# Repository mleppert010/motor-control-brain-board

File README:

May as well make a readme
Brain board for motor controller

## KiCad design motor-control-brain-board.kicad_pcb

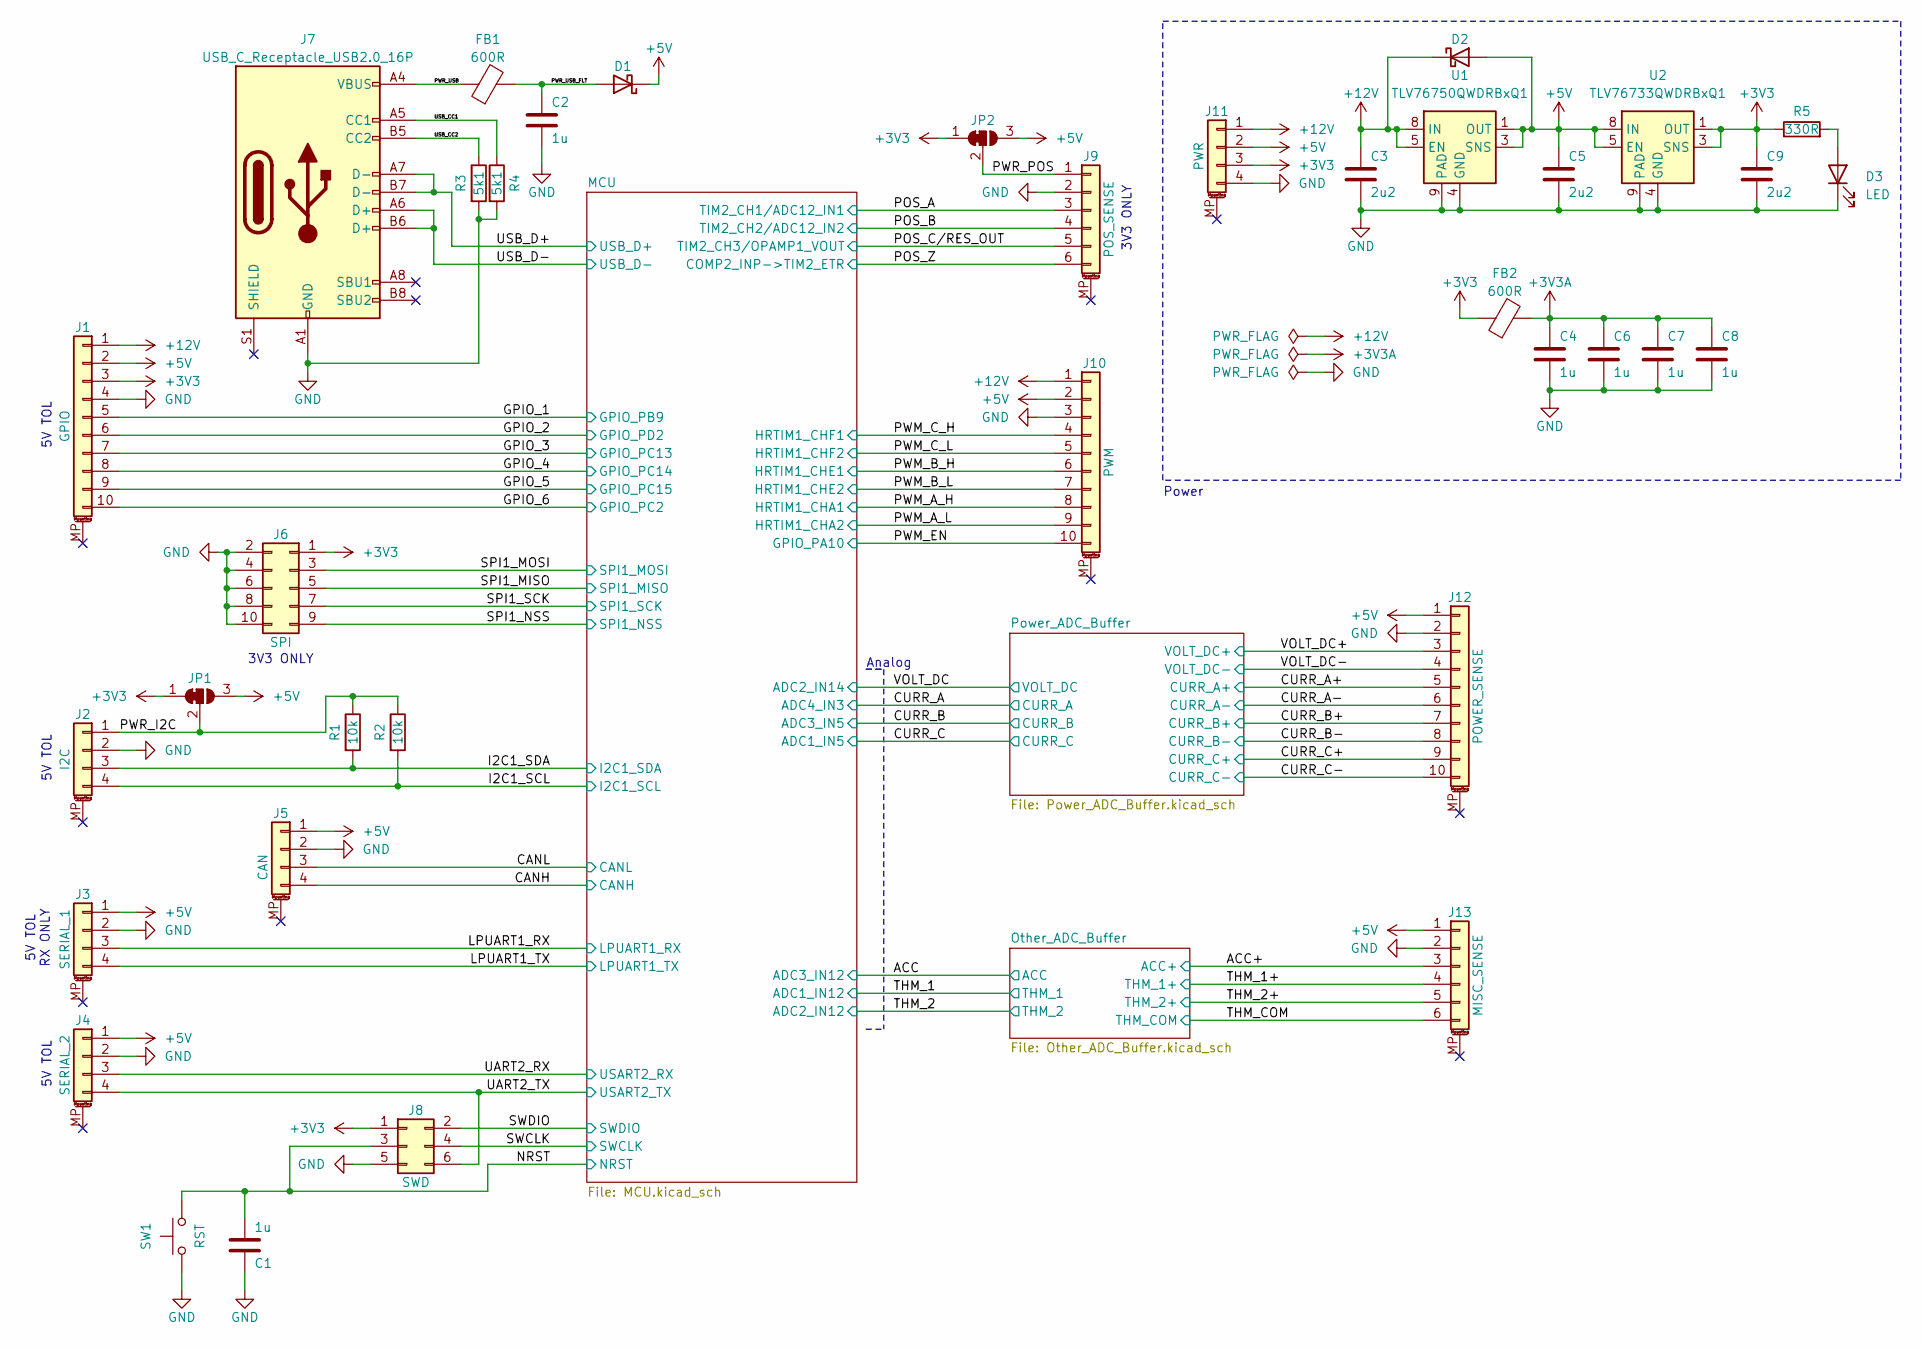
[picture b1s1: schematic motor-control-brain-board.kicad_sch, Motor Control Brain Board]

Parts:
C1, C2, C4, C6, C7, C8: 1u; C_0402_1005Metric
C3, C5, C9: 2u2; C_0603_1608Metric
D1, D2: D_Schottky; D_0402_1005Metric
D3: LED; LED_0603_1608Metric
FB1, FB2: 600R; L_0603_1608Metric
J1: GPIO; JST_GH_SM10B-GHS-TB_1x10-1MP_P1.25mm_Horizontal
J2: I2C; JST_GH_SM04B-GHS-TB_1x04-1MP_P1.25mm_Horizontal
J3: SERIAL_1; JST_GH_SM04B-GHS-TB_1x04-1MP_P1.25mm_Horizontal
J4: SERIAL_2; JST_GH_SM04B-GHS-TB_1x04-1MP_P1.25mm_Horizontal
J5: CAN; JST_GH_SM04B-GHS-TB_1x04-1MP_P1.25mm_Horizontal
J6: SPI; PinHeader_2x05_P1.27mm_Vertical
J7: USB_C_Receptacle_USB2.0_16P; USB_C_Receptacle_GCT_USB4110
J8: SWD; Tag-Connect_TC2030-IDC-FP_2x03_P1.27mm_Vertical
J9: POS_SENSE; JST_GH_SM06B-GHS-TB_1x06-1MP_P1.25mm_Horizontal
J10: PWM; JST_GH_SM10B-GHS-TB_1x10-1MP_P1.25mm_Horizontal
J11: PWR; JST_GH_SM04B-GHS-TB_1x04-1MP_P1.25mm_Horizontal
J12: POWER_SENSE; JST_GH_SM10B-GHS-TB_1x10-1MP_P1.25mm_Horizontal
J13: MISC_SENSE; JST_GH_SM06B-GHS-TB_1x06-1MP_P1.25mm_Horizontal
JP1, JP2: SolderJumper_3_Open; SolderJumper-3_P1.3mm_Bridged12_RoundedPad1.0x1.5mm
R1, R2: 10k; R_0402_1005Metric
R3, R4: 5k1; R_0402_1005Metric
R5: 330R; R_0402_1005Metric
SW1: RST; SW_SPST_PTS810
U1: TLV76750QWDRBxQ1; VSON-8-1EP_3x3mm_P0.65mm_EP1.65x2.4mm_ThermalVias
U2: TLV76733QWDRBxQ1; VSON-8-1EP_3x3mm_P0.65mm_EP1.65x2.4mm_ThermalVias

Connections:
+3V3: C9.1, FB2.1, J1.3, J6.1, J8.1, J11.3, JP1.1 (A), JP2.1 (A), R5.1, U2.1 (OUT), U2.3 (SNS); also elsewhere on the board
+3V3A: C4.1, C6.1, C7.1, C8.1, FB2.2; also elsewhere on the board
+5V: C5.1, D1.1 (K), D2.2 (A), J1.2, J3.1, J4.1, J5.1, J10.2, J11.2, J12.1, J13.1, JP1.3 (B), JP2.3 (B), U1.1 (OUT), U1.3 (SNS), U2.5 (EN), U2.8 (IN); also elsewhere on the board
+12V: C3.1, D2.1 (K), J1.1, J10.1, J11.1, U1.5 (EN), U1.8 (IN)
/ACC+: J13.3; also elsewhere on the board
/CANH: J5.4; also elsewhere on the board
/CANL: J5.3; also elsewhere on the board
/CURR_A+: J12.5; also elsewhere on the board
/CURR_A-: J12.6; also elsewhere on the board
/CURR_B+: J12.7; also elsewhere on the board
/CURR_B-: J12.8; also elsewhere on the board
/CURR_C+: J12.9; also elsewhere on the board
/CURR_C-: J12.10; also elsewhere on the board
/GPIO_1: J1.5; also elsewhere on the board
/GPIO_2: J1.6; also elsewhere on the board
/GPIO_3: J1.7; also elsewhere on the board
/GPIO_4: J1.8; also elsewhere on the board
/GPIO_5: J1.9; also elsewhere on the board
/GPIO_6: J1.10; also elsewhere on the board
/I2C1_SCL: J2.4, R2.2; also elsewhere on the board
/I2C1_SDA: J2.3, R1.2; also elsewhere on the board
/LPUART1_RX: J3.3; also elsewhere on the board
/LPUART1_TX: J3.4; also elsewhere on the board
/NRST: C1.2, J8.3, SW1.2; also elsewhere on the board
/POS_A: J9.3; also elsewhere on the board
/POS_B: J9.4; also elsewhere on the board
/POS_C/RES_OUT: J9.5; also elsewhere on the board
/POS_Z: J9.6; also elsewhere on the board
/PWM_A_H: J10.8; also elsewhere on the board
/PWM_A_L: J10.9; also elsewhere on the board
/PWM_B_H: J10.6; also elsewhere on the board
/PWM_B_L: J10.7; also elsewhere on the board
/PWM_C_H: J10.4; also elsewhere on the board
/PWM_C_L: J10.5; also elsewhere on the board
/PWM_EN: J10.10; also elsewhere on the board
/PWR_I2C: J2.1, JP1.2 (C), R1.1, R2.1
/PWR_POS: J9.1, JP2.2 (C)
/PWR_USB: FB1.1, J7.A4 (VBUS), J7.A9 (VBUS), J7.B4 (VBUS), J7.B9 (VBUS)
/PWR_USB_FLT: C2.1, D1.2 (A), FB1.2
/SPI1_MISO: J6.5; also elsewhere on the board
/SPI1_MOSI: J6.3; also elsewhere on the board
/SPI1_NSS: J6.9; also elsewhere on the board
/SPI1_SCK: J6.7; also elsewhere on the board
/SWCLK: J8.4; also elsewhere on the board
/SWDIO: J8.2; also elsewhere on the board
/THM_1+: J13.4; also elsewhere on the board
/THM_2+: J13.5; also elsewhere on the board
/UART2_RX: J4.3; also elsewhere on the board
/UART2_TX: J4.4, J8.6; also elsewhere on the board
/USB_CC1: J7.A5 (CC1), R4.1
/USB_CC2: J7.B5 (CC2), R3.1
/USB_D+: J7.A7 (D-), J7.B7 (D-); also elsewhere on the board
/USB_D-: J7.A6 (D+), J7.B6 (D+); also elsewhere on the board
/VOLT_DC+: J12.3; also elsewhere on the board
/VOLT_DC-: J12.4; also elsewhere on the board
GND: C1.1, C2.2, C3.2, C4.2, C5.2, C6.2, C7.2, C8.2, C9.2, D3.1 (K), J1.4, J2.2, J3.2, J4.2, J5.2, J6.2, J6.4, J6.6, J6.8, J6.10, J7.A1 (GND), J7.A12 (GND), J7.B1 (GND), J7.B12 (GND), J8.5, J9.2, J10.3, J11.4, J12.2, J13.2, J13.6, R3.2, R4.2, SW1.1, U1.4 (GND), U1.6 (GND), U1.9 (PAD), U2.4 (GND), U2.6 (GND), U2.9 (PAD); also elsewhere on the board
unnamed: D3.2 (A), R5.2

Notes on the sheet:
5V TOL RX ONLY
3V3 ONLY
Analog
Power
5V TOL

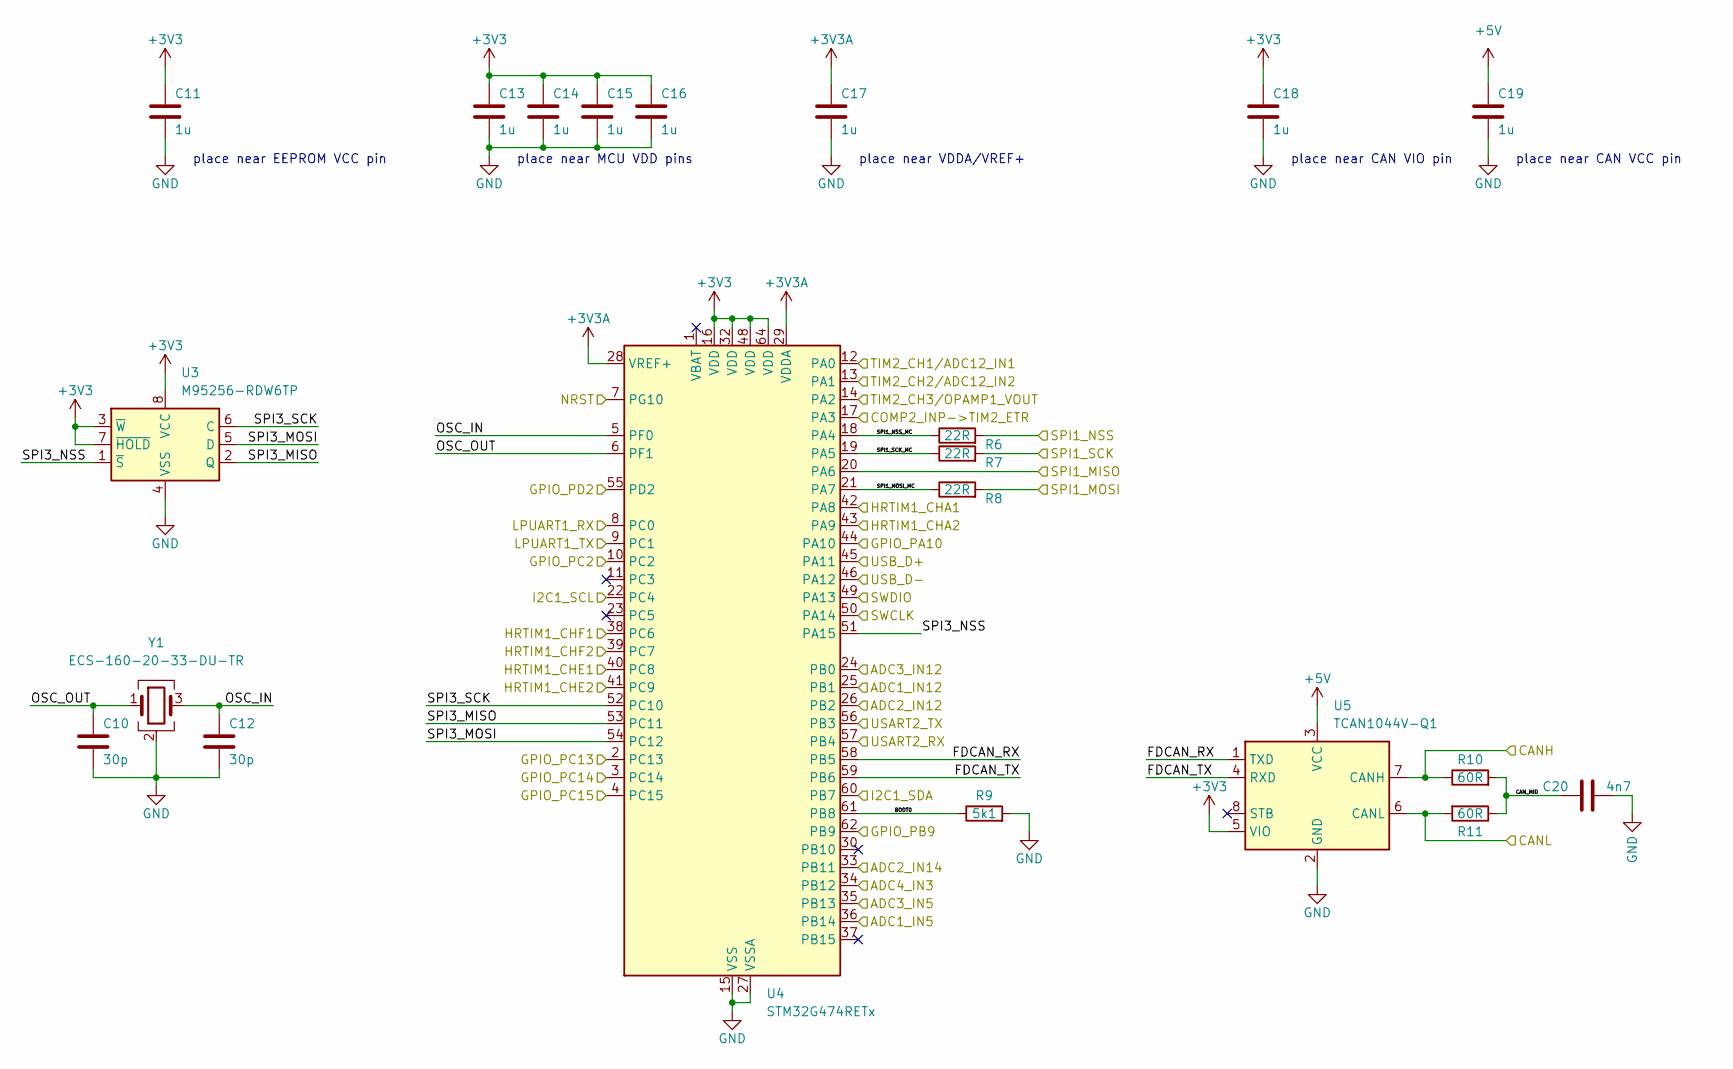
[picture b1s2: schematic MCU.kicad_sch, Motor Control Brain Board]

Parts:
C10, C12: 30p; C_0402_1005Metric
C11, C13, C14, C15, C16, C17, C18, C19: 1u; C_0402_1005Metric
C20: 4n7; C_0402_1005Metric
R6, R7, R8: 22R; R_0402_1005Metric
R9: 5k1; R_0402_1005Metric
R10, R11: 60R; R_0603_1608Metric
U3: M95256-RDW6TP; TSSOP-8_4.4x3mm_P0.65mm
U4: STM32G474RETx; LQFP-64_10x10mm_P0.5mm
U5: TCAN1044V-Q1; TSOT-23-8
Y1: ECS-160-20-33-DU-TR; Oscillator_SMD_Abracon_ASE-4Pin_3.2x2.5mm

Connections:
+3V3: C11.1, C13.1, C14.1, C15.1, C16.1, C18.1, U3.3 (~W), U3.7 (~HOLD), U3.8 (VCC), U4.16 (VDD), U4.32 (VDD), U4.48 (VDD), U4.64 (VDD), U5.5 (VIO); also elsewhere on the board
+3V3A: C17.1, U4.28 (VREF+), U4.29 (VDDA); also elsewhere on the board
+5V: C19.1, U5.3 (VCC); also elsewhere on the board
/ACC: U4.24 (PB0); also elsewhere on the board
/CANH: R10.1, U5.7 (CANH); also elsewhere on the board
/CANL: R11.2, U5.6 (CANL); also elsewhere on the board
/CURR_A: U4.34 (PB12); also elsewhere on the board
/CURR_B: U4.35 (PB13); also elsewhere on the board
/CURR_C: U4.36 (PB14); also elsewhere on the board
/GPIO_1: U4.62 (PB9); also elsewhere on the board
/GPIO_2: U4.55 (PD2); also elsewhere on the board
/GPIO_3: U4.2 (PC13); also elsewhere on the board
/GPIO_4: U4.3 (PC14); also elsewhere on the board
/GPIO_5: U4.4 (PC15); also elsewhere on the board
/GPIO_6: U4.10 (PC2); also elsewhere on the board
/I2C1_SCL: U4.22 (PC4); also elsewhere on the board
/I2C1_SDA: U4.60 (PB7); also elsewhere on the board
/LPUART1_RX: U4.8 (PC0); also elsewhere on the board
/LPUART1_TX: U4.9 (PC1); also elsewhere on the board
/MCU/BOOT0: R9.1, U4.61 (PB8)
/MCU/CAN_MID: C20.1, R10.2, R11.1
/MCU/FDCAN_RX: U4.58 (PB5), U5.1 (TXD)
/MCU/FDCAN_TX: U4.59 (PB6), U5.4 (RXD)
/MCU/OSC_IN: C12.1, U4.5 (PF0), Y1.3
/MCU/OSC_OUT: C10.1, U4.6 (PF1), Y1.1
/MCU/SPI1_MOSI_MC: R8.1, U4.21 (PA7)
/MCU/SPI1_NSS_MC: R6.1, U4.18 (PA4)
/MCU/SPI1_SCK_MC: R7.1, U4.19 (PA5)
/MCU/SPI3_MISO: U3.2 (Q), U4.53 (PC11)
/MCU/SPI3_MOSI: U3.5 (D), U4.54 (PC12)
/MCU/SPI3_NSS: U3.1 (~S), U4.51 (PA15)
/MCU/SPI3_SCK: U3.6 (C), U4.52 (PC10)
/NRST: U4.7 (PG10); also elsewhere on the board
/POS_A: U4.12 (PA0); also elsewhere on the board
/POS_B: U4.13 (PA1); also elsewhere on the board
/POS_C/RES_OUT: U4.14 (PA2); also elsewhere on the board
/POS_Z: U4.17 (PA3); also elsewhere on the board
/PWM_A_H: U4.42 (PA8); also elsewhere on the board
/PWM_A_L: U4.43 (PA9); also elsewhere on the board
/PWM_B_H: U4.40 (PC8); also elsewhere on the board
/PWM_B_L: U4.41 (PC9); also elsewhere on the board
/PWM_C_H: U4.38 (PC6); also elsewhere on the board
/PWM_C_L: U4.39 (PC7); also elsewhere on the board
/PWM_EN: U4.44 (PA10); also elsewhere on the board
/SPI1_MISO: U4.20 (PA6); also elsewhere on the board
/SPI1_MOSI: R8.2; also elsewhere on the board
/SPI1_NSS: R6.2; also elsewhere on the board
/SPI1_SCK: R7.2; also elsewhere on the board
/SWCLK: U4.50 (PA14); also elsewhere on the board
/SWDIO: U4.49 (PA13); also elsewhere on the board
/THM_1: U4.25 (PB1); also elsewhere on the board
/THM_2: U4.26 (PB2); also elsewhere on the board
/UART2_RX: U4.57 (PB4); also elsewhere on the board
/UART2_TX: U4.56 (PB3); also elsewhere on the board
/USB_D+: U4.45 (PA11); also elsewhere on the board
/USB_D-: U4.46 (PA12); also elsewhere on the board
/VOLT_DC: U4.33 (PB11); also elsewhere on the board
GND: C10.2, C11.2, C12.2, C13.2, C14.2, C15.2, C16.2, C17.2, C18.2, C19.2, C20.2, R9.2, U3.4 (VSS), U4.15 (VSS), U4.27 (VSSA), U4.31 (VSS), U4.47 (VSS), U4.63 (VSS), U5.2 (GND), Y1.2 (G), Y1.4 (G); also elsewhere on the board

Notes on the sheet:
place near EEPROM VCC pin
place near MCU VDD pins
place near VDDA/VREF+
place near CAN VIO pin
place near CAN VCC pin

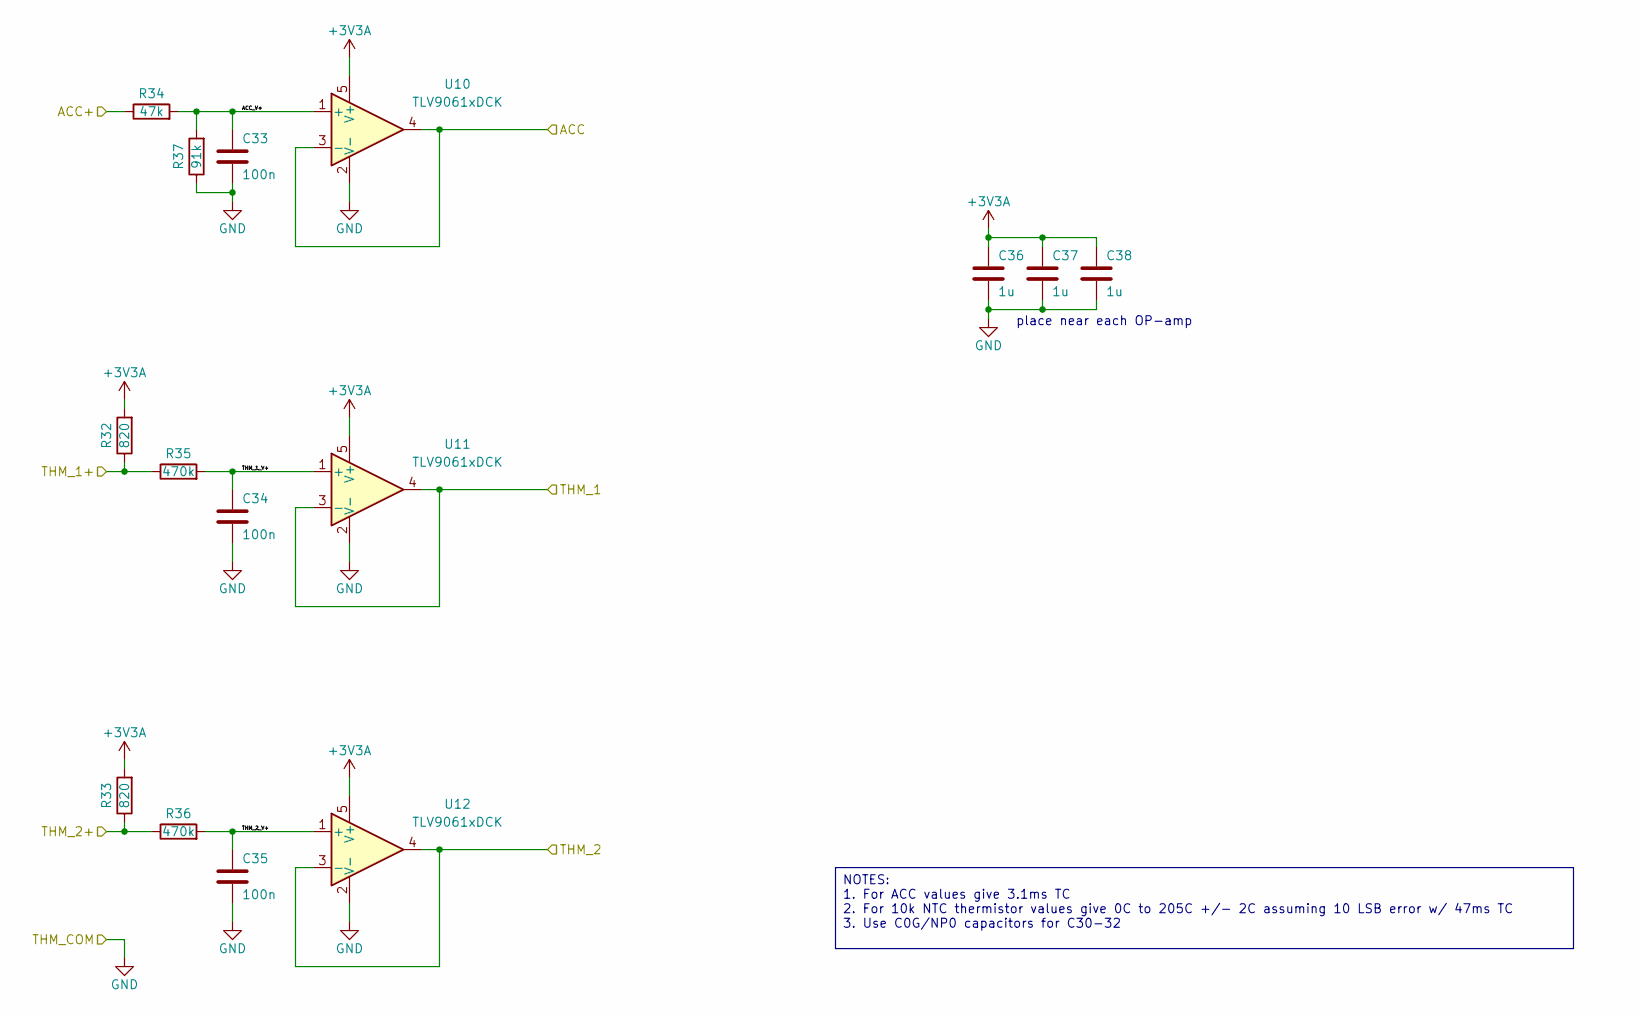
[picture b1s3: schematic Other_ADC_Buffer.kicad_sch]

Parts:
C33, C34, C35: 100n; C_0603_1608Metric
C36, C37, C38: 1u; C_0402_1005Metric
R32, R33: 820; R_0603_1608Metric
R34: 47k; R_0603_1608Metric
R35, R36: 470k; R_0603_1608Metric
R37: 91k; R_0603_1608Metric
U10, U11, U12: TLV9061xDCK; SOT-353_SC-70-5

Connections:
+3V3A: C36.1, C37.1, C38.1, R32.2, R33.2, U10.5 (V+), U11.5 (V+), U12.5 (V+); also elsewhere on the board
/ACC: U10.3 (-), U10.4; also elsewhere on the board
/ACC+: R34.1; also elsewhere on the board
/Other_ADC_Buffer/ACC_V+: C33.1, R34.2, R37.2, U10.1 (+)
/Other_ADC_Buffer/THM_1_V+: C34.1, R35.2, U11.1 (+)
/Other_ADC_Buffer/THM_2_V+: C35.1, R36.2, U12.1 (+)
/THM_1: U11.3 (-), U11.4; also elsewhere on the board
/THM_1+: R32.1, R35.1; also elsewhere on the board
/THM_2: U12.3 (-), U12.4; also elsewhere on the board
/THM_2+: R33.1, R36.1; also elsewhere on the board
GND: C33.2, C34.2, C35.2, C36.2, C37.2, C38.2, R37.1, U10.2 (V-), U11.2 (V-), U12.2 (V-); also elsewhere on the board

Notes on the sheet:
place near each OP-amp
NOTES: 1. For ACC values give 3.1ms TC 2. For 10k NTC thermistor values give 0C to 205C +/- 2C assuming 10 LSB error w/ 47ms TC 3. Use C0G/NP0 capacitors for C30-32

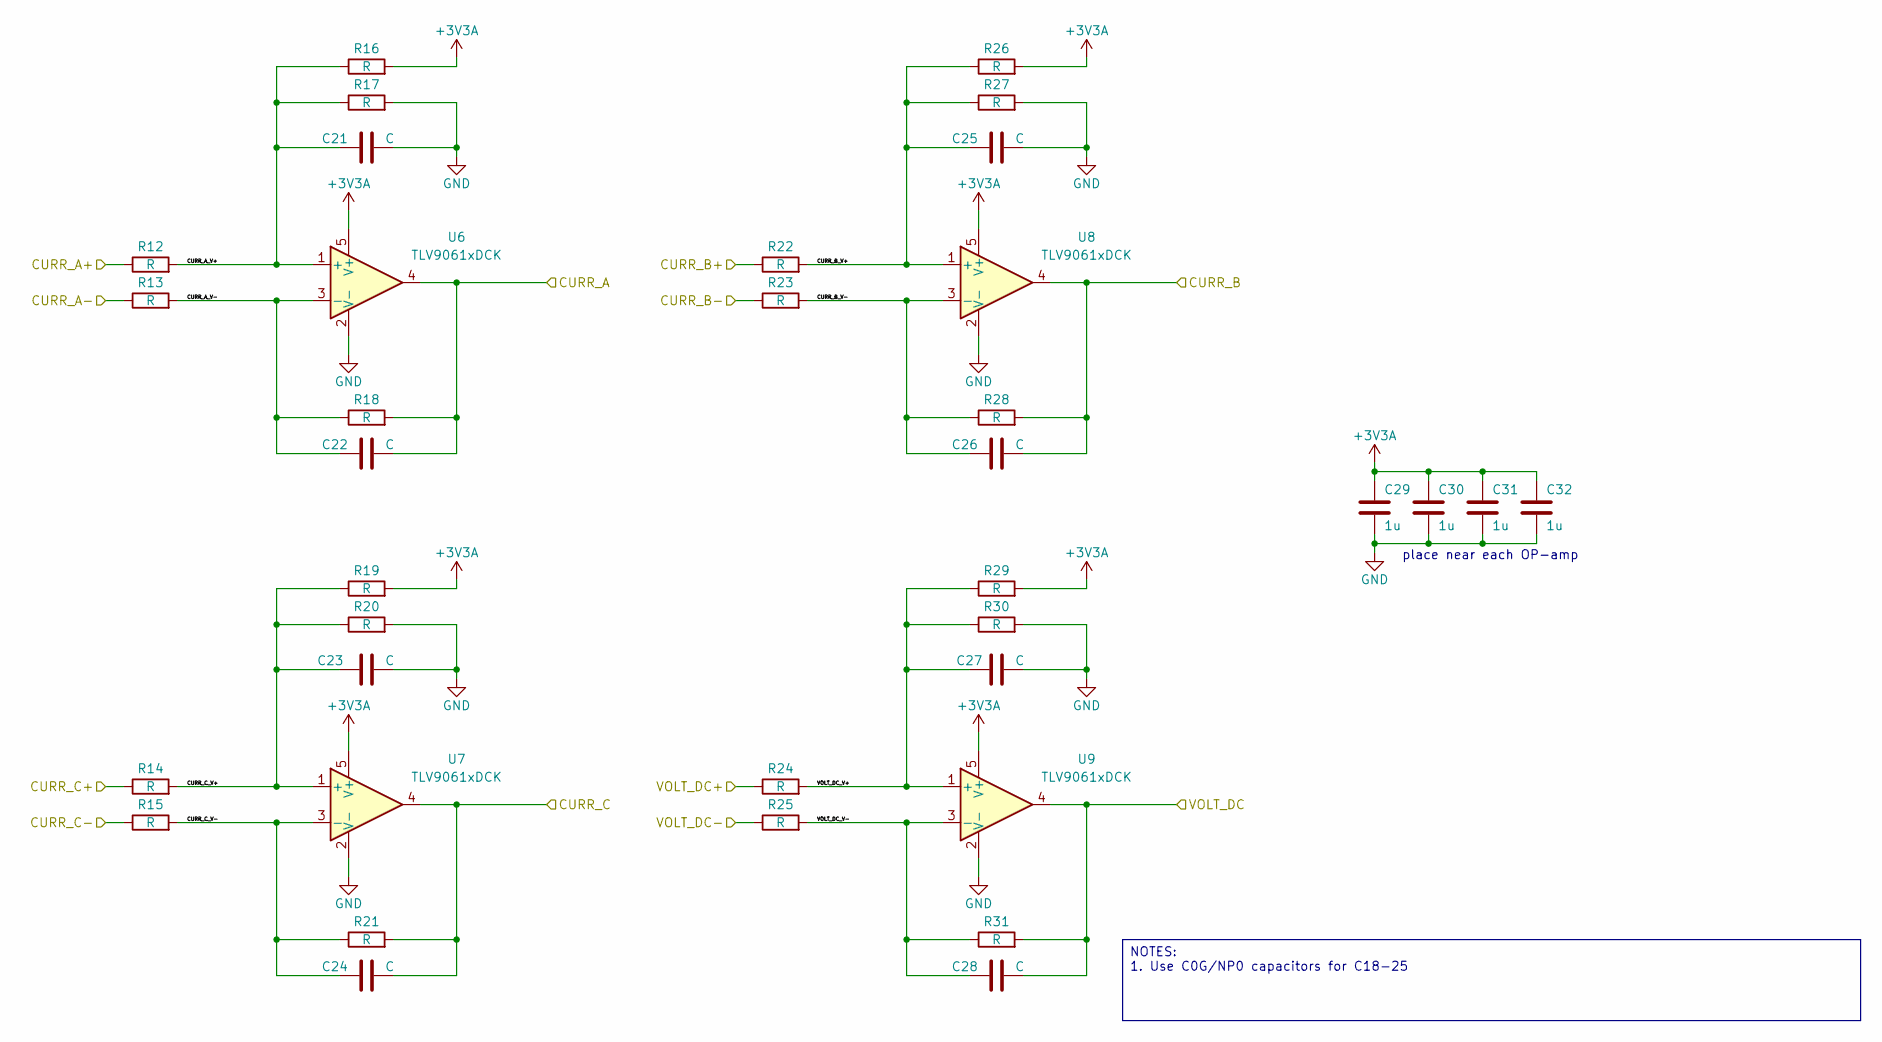
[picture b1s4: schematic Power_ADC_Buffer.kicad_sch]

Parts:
C21, C22, C23, C24, C25, C26, C27, C28: C; C_0603_1608Metric
C29, C30, C31, C32: 1u; C_0402_1005Metric
R12, R13, R14, R15, R16, R17, R18, R19, R20, R21, R22, R23, R24, R25, R26, R27, R28, R29, R30, R31: R; R_0603_1608Metric
U6, U7, U8, U9: TLV9061xDCK; SOT-353_SC-70-5

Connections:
+3V3A: C29.1, C30.1, C31.1, C32.1, R16.2, R19.2, R26.2, R29.2, U6.5 (V+), U7.5 (V+), U8.5 (V+), U9.5 (V+); also elsewhere on the board
/CURR_A: C22.2, R18.2, U6.4; also elsewhere on the board
/CURR_A+: R12.1; also elsewhere on the board
/CURR_A-: R13.1; also elsewhere on the board
/CURR_B: C26.2, R28.2, U8.4; also elsewhere on the board
/CURR_B+: R22.1; also elsewhere on the board
/CURR_B-: R23.1; also elsewhere on the board
/CURR_C: C24.2, R21.2, U7.4; also elsewhere on the board
/CURR_C+: R14.1; also elsewhere on the board
/CURR_C-: R15.1; also elsewhere on the board
/Power_ADC_Buffer/CURR_A_V+: C21.1, R12.2, R16.1, R17.1, U6.1 (+)
/Power_ADC_Buffer/CURR_A_V-: C22.1, R13.2, R18.1, U6.3 (-)
/Power_ADC_Buffer/CURR_B_V+: C25.1, R22.2, R26.1, R27.1, U8.1 (+)
/Power_ADC_Buffer/CURR_B_V-: C26.1, R23.2, R28.1, U8.3 (-)
/Power_ADC_Buffer/CURR_C_V+: C23.1, R14.2, R19.1, R20.1, U7.1 (+)
/Power_ADC_Buffer/CURR_C_V-: C24.1, R15.2, R21.1, U7.3 (-)
/Power_ADC_Buffer/VOLT_DC_V+: C27.1, R24.2, R29.1, R30.1, U9.1 (+)
/Power_ADC_Buffer/VOLT_DC_V-: C28.1, R25.2, R31.1, U9.3 (-)
/VOLT_DC: C28.2, R31.2, U9.4; also elsewhere on the board
/VOLT_DC+: R24.1; also elsewhere on the board
/VOLT_DC-: R25.1; also elsewhere on the board
GND: C21.2, C23.2, C25.2, C27.2, C29.2, C30.2, C31.2, C32.2, R17.2, R20.2, R27.2, R30.2, U6.2 (V-), U7.2 (V-), U8.2 (V-), U9.2 (V-); also elsewhere on the board

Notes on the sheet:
place near each OP-amp
NOTES: 1. Use C0G/NP0 capacitors for C18-25

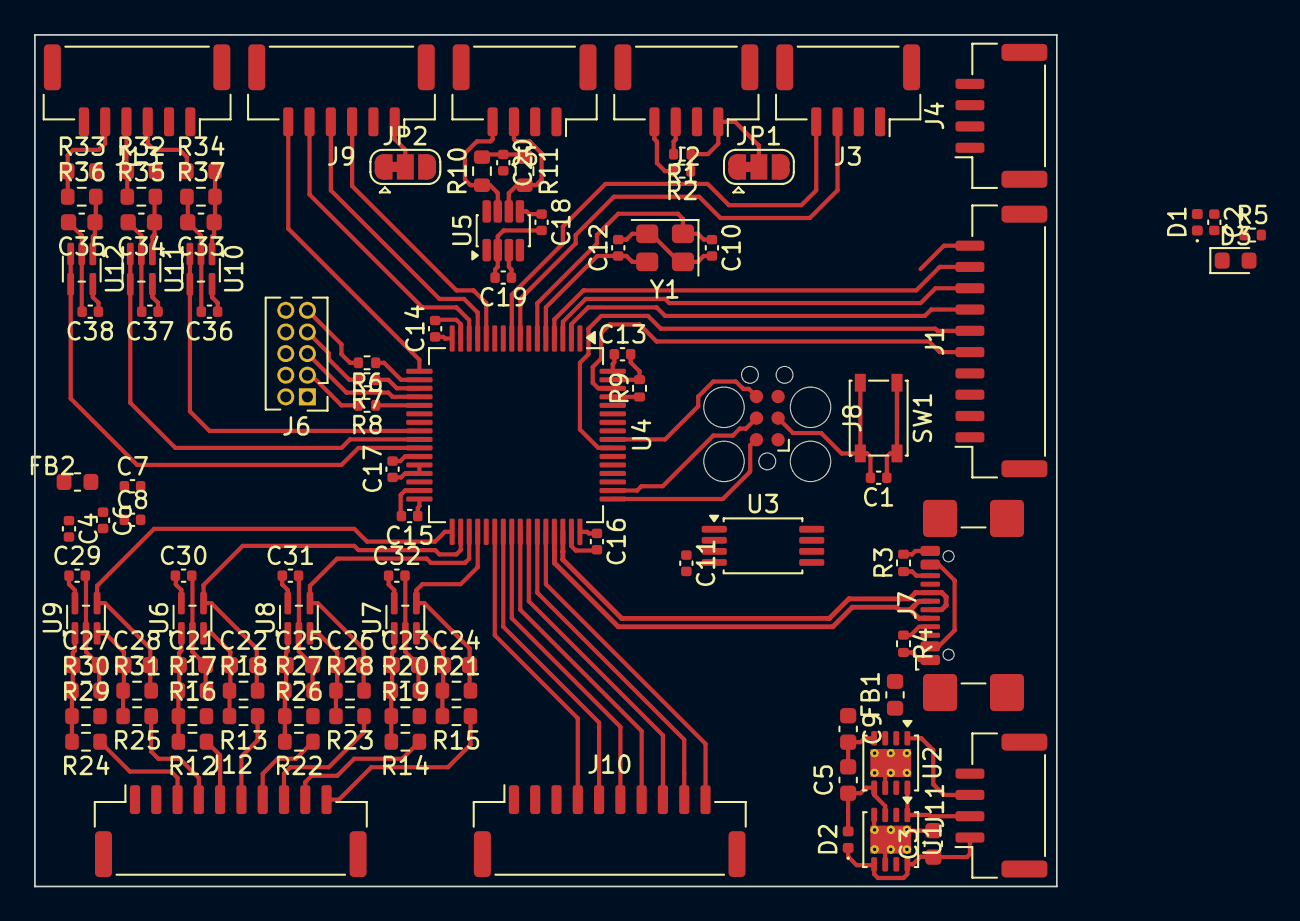
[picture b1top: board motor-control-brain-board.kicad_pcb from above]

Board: 4 copper layers, 60.0 x 50.0 mm, 109 parts (0 on the bottom side), 88 nets.

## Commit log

2025-11-10 Updated schematic to use HRTIM1 and reviewed
2025-11-11 Deleted old files
2025-11-11 Started routing PCB
2025-11-12 Routed Stuff
2025-11-12 Made board size exactly 50mmx60mm
2026-01-28 Continued work on PCB layout, think I should add castellated holes as an alternative to connectors
2026-01-29 Moved connectors for IO to 'external' edges and connectors for inverter to 'interior' edges
2026-02-02 Changed +3V3 to +3v3A for thermistor supplies
2026-02-06 Changed EEPROM to TSSOT for smallness
2026-02-06 added .gitignore
2026-02-06 fixed files
2026-02-06 Added Readme
2026-02-07 Moved MCU to create room on top of board
2026-02-09 Changed to LPUART for 1 channel to improve routing etc. Can now add 1 more ADC as needed. Todo: Figure out GPIO and add oscillator
2026-02-09 Figured out GPIO and added oscillator to schematic, need to pick part
2026-02-11 Updated PCB net colors
2026-02-11 Moved MCU to make more room for routing, updated crystal package/PN
2026-02-11 Routing
2026-02-11 Adjusted cap sizes, 0603 for all need hand soldering, 0402 where possible, 0804 as needed
2026-02-12 Changed op Amp, need to reroute, need to re-asses capacitor situation since || 0.1 and 1 is dumb. Just use 2 1s in that case.
2026-02-12 Cheaper, smaller 10MHz Op Amp
2026-02-13 Rerouting stuff
2026-02-13 Added voltage spec to POS sensor
2026-02-13 Updating all decoupling to 1u
2026-02-14 did stuff
